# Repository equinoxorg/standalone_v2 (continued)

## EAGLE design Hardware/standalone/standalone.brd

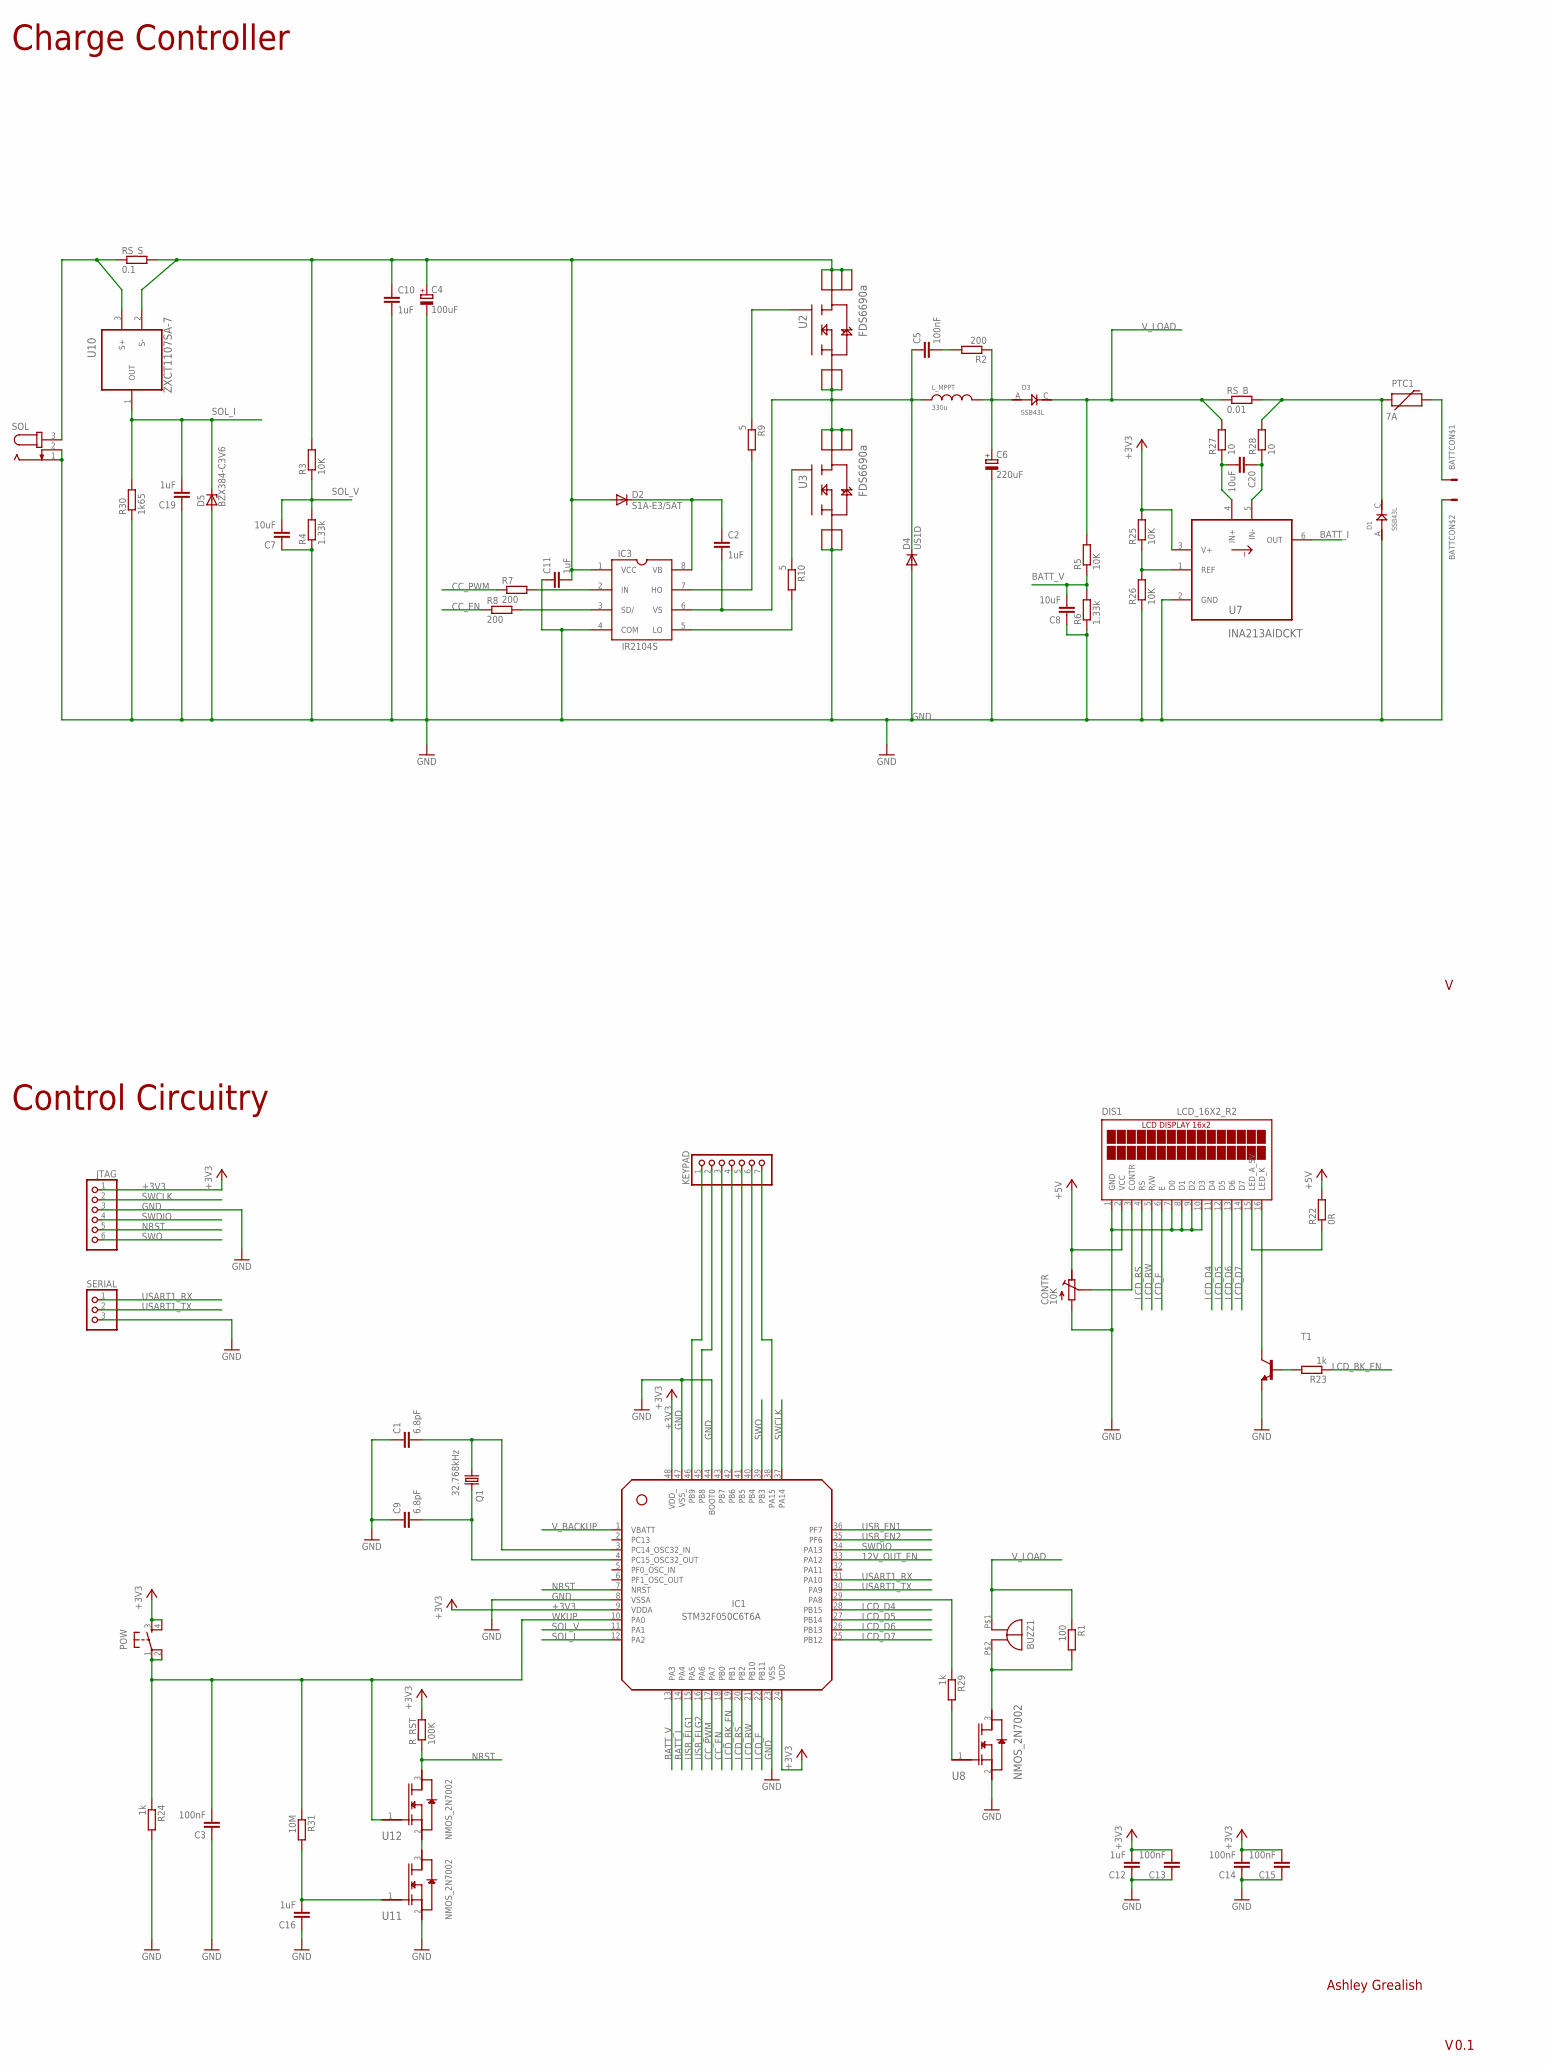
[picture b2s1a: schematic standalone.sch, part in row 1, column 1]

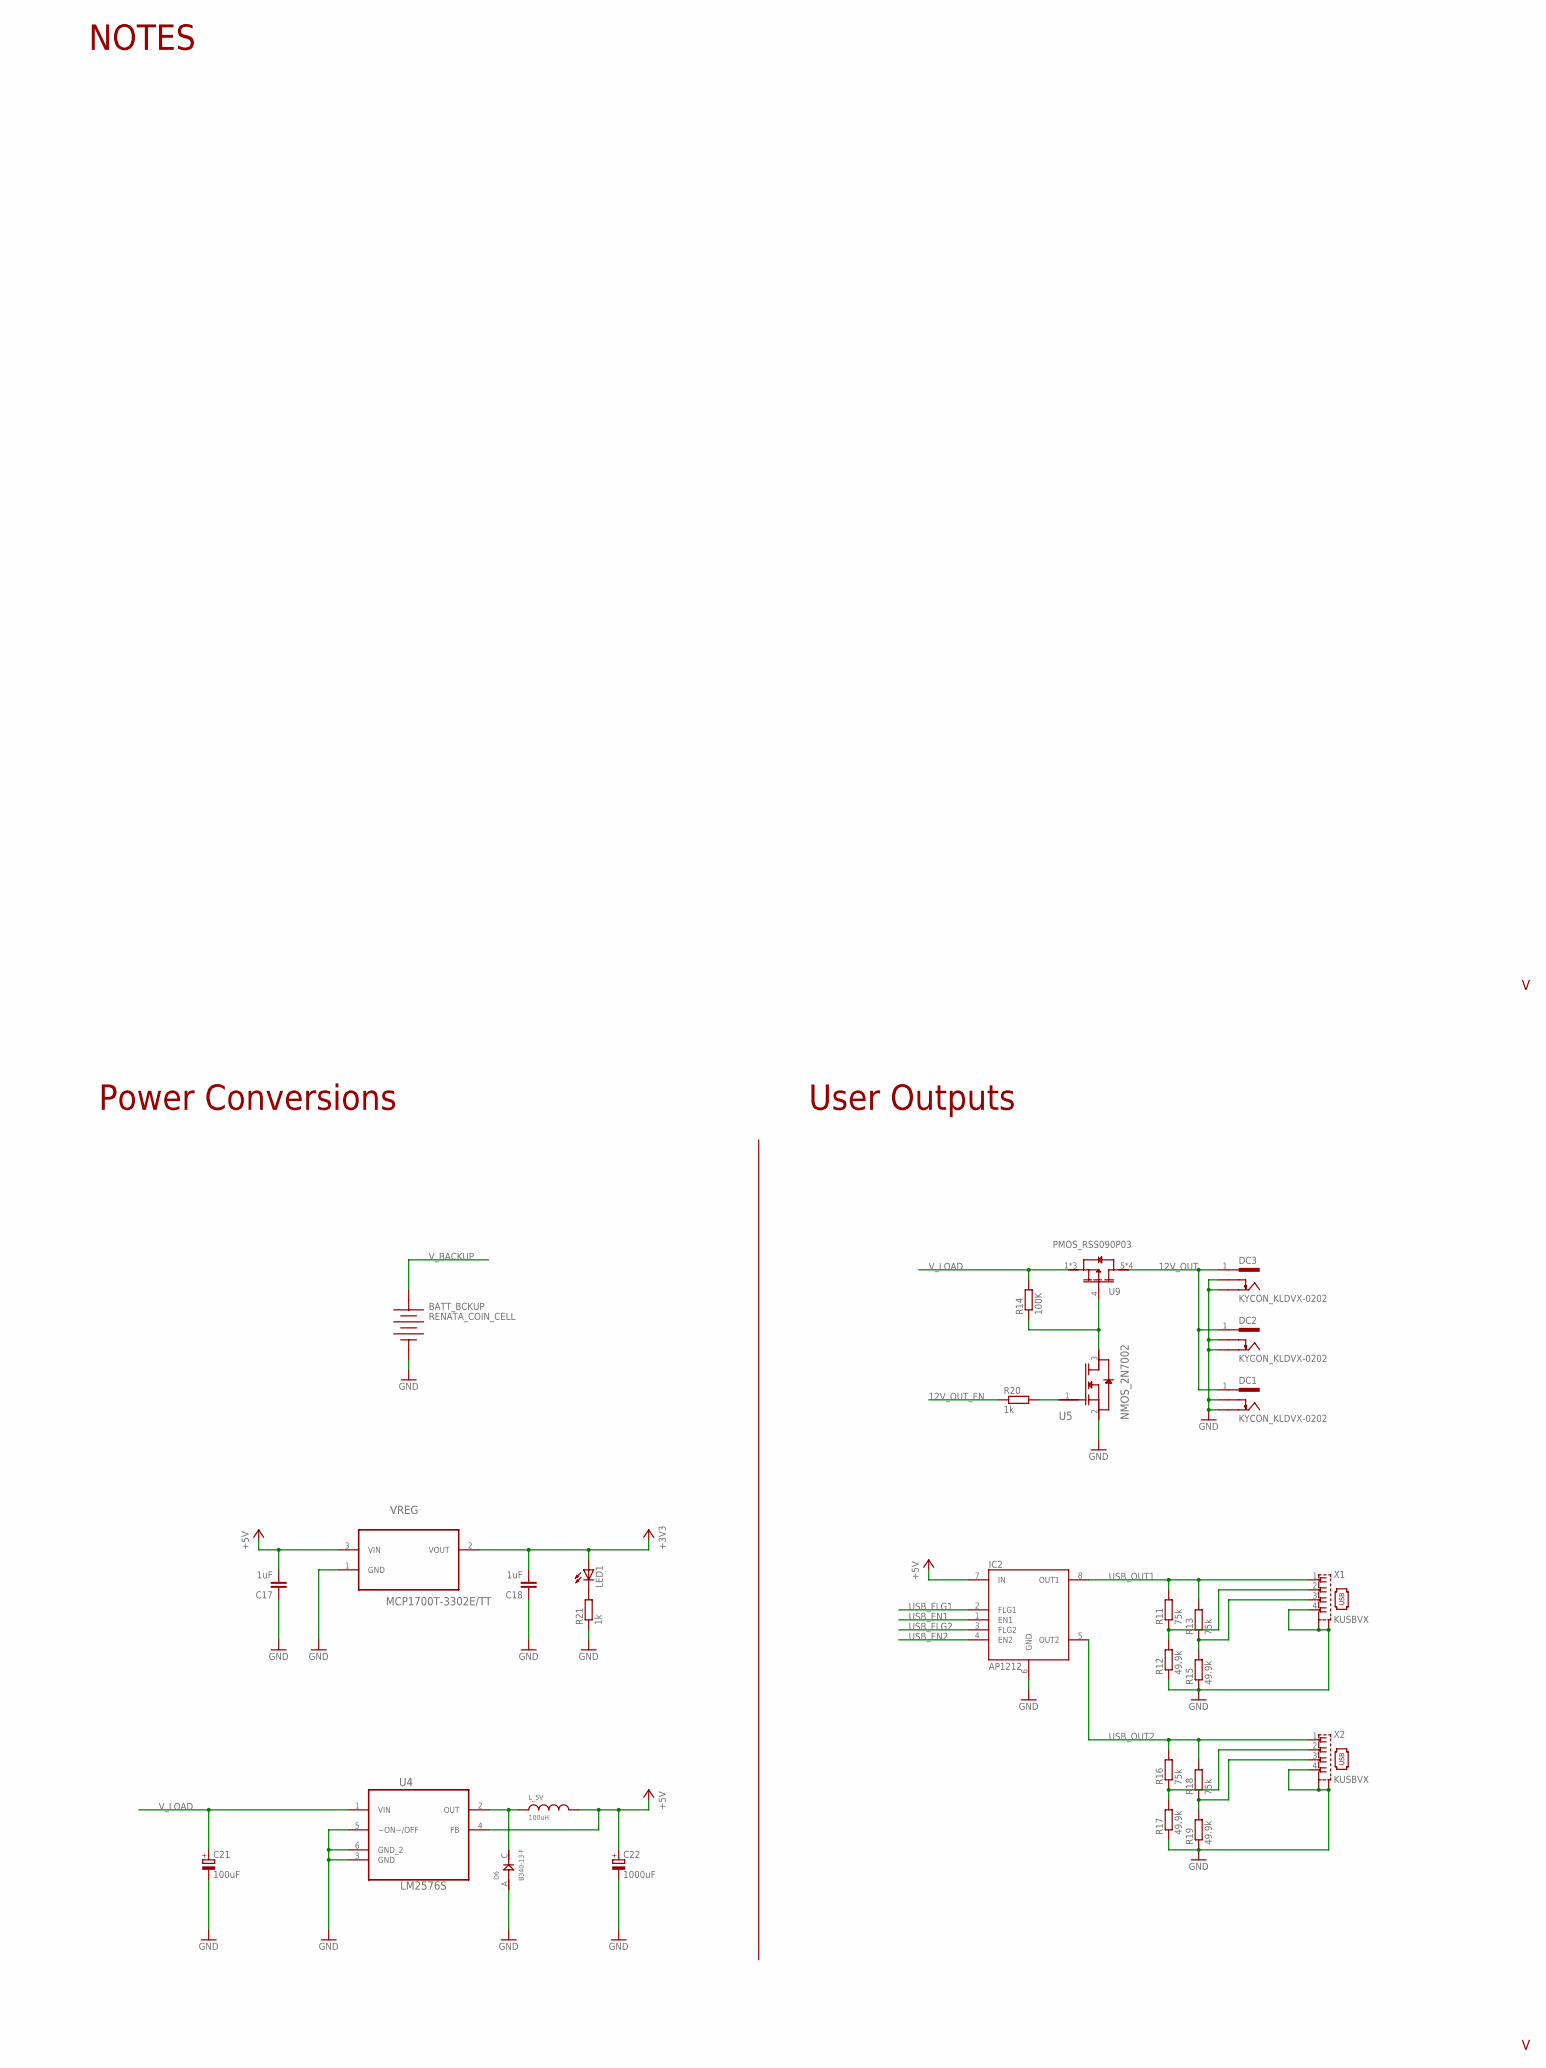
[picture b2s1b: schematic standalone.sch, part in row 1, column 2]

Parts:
BATT: CON_MOLEX_39_29_1028; MOLEX_39_29_1028
BATT_BCKUP: RENATA_COIN_CELL; PANASONIC_CR2032_1298246
BUZZ1: BUZZ_14MM; BUZZ_14MM_5M_PINS
C1, C9: 6.8pF; C0603K
C2, C10, C11, C12, C16, C17, C18, C19: 1uF; C0805K
C3, C5, C13, C14, C15: 100nF; C0805K
C4, C21: 100uF; PANASONIC_E
C6: 220uF; PANASONIC_F
C7, C8, C20: 10uF; C0805K
C22: 1000uF; PANASONIC_G
CONTR: 10K; R_TRIMM_RC33X
D1, D3: SSB43L; DO214AA
D2: S1A-E3/5AT; DO-214AC
D4: US1D; DO-214AC
D5: BZX384-C3V6; SOD323
D6: B340-13-F; SMC
DC1, DC2, DC3: KYCON_KLDVX-0202; KYCON_KLVDX_2020_B
DIS1: LCD_16X2_R2
IC1: STM32F050C6T6A; LQFP48
IC2: AP1212; SO8
IC3: IR2104S
JTAG: PINHD-1X6; 1X06
KEYPAD: PINHD-1X7/90; 1X07/90
LED1: POW_3V3; CHIPLED_0805
L_5V: 100uH; INDUC_BOURNS_SDR2207
L_MPPT: 330u; INDUC_BOURNS_SDR1806
POW: TAC_SWITCHPTH; TACTILE-PTH
PTC1: 7A; PTC_MF_R700
Q1: 32.768kHz; MC-306; MPN MC-306
R1: 100; M0805
R2, R7, R8: 200; M0805
R3, R5, R25, R26: 10K; M0805
R4, R6: 1.33k; M0805
R9, R10: 5; M0805
R11, R13, R16, R18: 75k; M0805
R12, R15, R17, R19: 49.9k; M0805
R14: 100K; M0805
R20, R21, R23, R24, R29: 1k; M0805
R22: 0R; M0805
R27, R28: 10; M0805
R30: 1k65; M0805
R31: 10M; M0805
RS_B: 0.01; R2512
RS_S: 0.1; R2512
R_RST: 100K; M0805
SERIAL: PINHD-1X3; 1X03
SOL: JACK-PLUG0; SPC4077
T1: BC847B-NPN-SOT23-BEC; SOT23-BEC
U2, U3: FDS6690a; SOIC127P600X175-8N
U4: LM2576S; TO263-5
U5: NMOS_2N7002; SOT103P240X110-3N
U7: INA213AIDCKT; SOT65P210X110-6N
U8, U11, U12: NMOS_2N7002; SOT103P240X110-3N; MPN 2N7002-7-F
U9: PMOS_RSS090P03; SO8
U10: ZXCT1107SA-7; SOT91P240X110-3N
U$1: EQUINOX_LOGO_LARGE
VREG: MCP1700T-3302E/TT; SOT95P237X112-3N
X1, X2: KUSBVX

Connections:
12V_OUT: DC1.1, DC2.1, DC3.1, U9.5 (D2), U9.6 (D2), U9.7 (D2), U9.8 (D2)
12V_OUT_EN: IC1.33 (PA12), R20.1
+3V3: C12.2, C13.2, C14.2, C15.2, C18.2, IC1.9 (VDDA), IC1.24 (VDD), IC1.48 (VDD_), JTAG.1, LED1.A, POW.3, POW.4, R25.2, R_RST.2, U7.3 (V+), VREG.2 (VOUT)
+5V: C17.2, C22.+, CONTR.CW (A), DIS1.2 (VCC), IC2.7 (IN), L_5V.P$2, R22.2, U4.4 (FB), VREG.3 (VIN)
BATT_I: IC1.14 (PA4), U7.6 (OUT)
BATT_V: C8.2, IC1.13 (PA3), R5.1, R6.2
CC_EN: IC1.18 (PB0), R8.1
CC_PWM: IC1.17 (PA7), R7.1
GND: BATT.P$2, BATT_BCKUP.P- (NEG), C1.1, C3.1, C4.-, C6.-, C7.1, C8.1, C9.1, C10.2, C11.1, C12.1, C13.1, C14.1, C15.1, C16.1, C17.1, C18.1, C19.1, C21.-, C22.-, CONTR.CCW (E), D1.A (ANODE), D4.A, D5.A, D6.A (ANODE), DC1.2, DC1.3, DC2.2, DC2.3, DC3.2, DC3.3, DIS1.1 (GND), DIS1.7 (D0), DIS1.8 (D1), DIS1.9 (D2), DIS1.10 (D3), IC1.8 (VSSA), IC1.23 (VSS), IC1.44 (BOOT0), IC1.47 (VSS_), IC2.6 (GND), IC3.4 (COM), JTAG.3, R4.1, R6.1, R12.1, R15.1, R17.1, R19.1, R21.1, R24.2, R26.1, R30.1, SERIAL.3, SOL.1, SOL.2, T1.E, U3.1 (S_2), U3.2 (S_3), U3.3 (S), U4.3 (GND), U4.5 (~ON~/OFF), U4.6 (GND_2), U5.2 (S), U7.2 (GND), U8.2 (S), U11.2 (S), VREG.1 (GND), X1.4, X1.M1 (S1), X1.M2 (S2), X2.4, X2.M1 (S1), X2.M2 (S2)
LCD_BK_EN: IC1.19 (PB1), R23.1
LCD_D4: DIS1.11 (D4), IC1.28 (PB15)
LCD_D5: DIS1.12 (D5), IC1.27 (PB14)
LCD_D6: DIS1.13 (D6), IC1.26 (PB13)
LCD_D7: DIS1.14 (D7), IC1.25 (PB12)
LCD_E: DIS1.6 (E), IC1.22 (PB11)
LCD_RS: DIS1.4 (RS), IC1.20 (PB2)
LCD_RW: DIS1.5 (R/W), IC1.21 (PB10)
unnamed: C1.2, IC1.3 (PC14_OSC32_IN), Q1.1
unnamed: CONTR.WIPE (S), DIS1.3 (CONTR)
unnamed: IC3.3 (SD/), R8.2
unnamed: D1.C (CATHODE), PTC1.P$1, R28.2, RS_B.2
unnamed: C2.2, C5.1, D4.C, IC3.6 (VS), L_MPPT.P$1, U2.1 (S_2), U2.2 (S_3), U2.3 (S), U3.5 (D_3), U3.6 (D_2), U3.7 (D_4), U3.8 (D)
unnamed: IC3.7 (HO), R9.2
unnamed: IC3.2 (IN), R7.2
unnamed: C2.1, D2.C, IC3.8 (VB)
unnamed: R10.1, U3.4 (G)
unnamed: C6.+, D3.A (ANODE), L_MPPT.P$2, R2.1
unnamed: IC3.5 (LO), R10.2
unnamed: R9.1, U2.4 (G)
unnamed: C5.2, R2.2
unnamed: C4.+, C10.1, C11.2, D2.A, IC3.1 (VCC), R3.2, RS_S.2, U2.5 (D_3), U2.6 (D_2), U2.7 (D_4), U2.8 (D), U10.2 (S-)
unnamed: C9.2, IC1.4 (PC15_OSC32_OUT), Q1.4 (2)
unnamed: DIS1.15 (LED_A_5V), R22.1
unnamed: R16.1, R17.2, X2.2
unnamed: D6.C (CATHODE), L_5V.P$1, U4.2 (OUT)
unnamed: IC1.29 (PA8), R29.1
unnamed: IC1.46 (PB9), KEYPAD.1
unnamed: IC1.45 (PB8), KEYPAD.2
unnamed: R14.1, U5.3 (D), U9.4 (G)
unnamed: IC1.43 (PB7), KEYPAD.3
unnamed: IC1.42 (PB6), KEYPAD.4
unnamed: IC1.41 (PB5), KEYPAD.5
unnamed: IC1.40 (PB4), KEYPAD.6
unnamed: IC1.38 (PA15), KEYPAD.7
unnamed: DIS1.16 (LED_K), T1.C
unnamed: R23.2, T1.B
unnamed: R11.1, R12.2, X1.2
unnamed: R13.1, R15.2, X1.3
unnamed: R20.2, U5.1 (G)
unnamed: R18.1, R19.2, X2.3
unnamed: LED1.C, R21.2
unnamed: RS_S.1, SOL.3, U10.3 (S+)
unnamed: R25.1, R26.2, U7.1 (REF)
unnamed: C20.2, R27.1, U7.4 (IN+)
unnamed: C20.1, R28.1, U7.5 (IN-)
unnamed: BUZZ1.P$2 (-), R1.2, U8.3 (D)
unnamed: R29.2, U8.1 (G)
unnamed: C16.2, R31.2, U11.1 (G)
unnamed: U11.3 (D), U12.2 (S)
unnamed: BATT.P$1, PTC1.P$2
NRST: IC1.7 (NRST), JTAG.5, R_RST.1, U12.3 (D)
SOL_I: C19.2, D5.C, IC1.12 (PA2), R30.2, U10.1 (OUT)
SOL_V: C7.2, IC1.11 (PA1), R3.1, R4.2
SWCLK: IC1.37 (PA14), JTAG.2
SWDIO: IC1.34 (PA13), JTAG.4
SWO: IC1.39 (PB3), JTAG.6
USART1_RX: IC1.31 (PA10), SERIAL.1
USART1_TX: IC1.30 (PA9), SERIAL.2
USB_EN1: IC1.36 (PF7), IC2.1 (EN1)
USB_EN2: IC1.35 (PF6), IC2.4 (EN2)
USB_FLG1: IC1.15 (PA5), IC2.2 (FLG1)
USB_FLG2: IC1.16 (PA6), IC2.3 (FLG2)
USB_OUT1: IC2.8 (OUT1), R11.2, R13.2, X1.1
USB_OUT2: IC2.5 (OUT2), R16.2, R18.2, X2.1
V_BACKUP: BATT_BCKUP.P+ (POS), IC1.1 (VBATT)
V_LOAD: BUZZ1.P$1 (+), C21.+, D3.C (CATHODE), R1.1, R5.2, R14.2, R27.2, RS_B.1, U4.1 (VIN), U9.1 (S2), U9.2 (S2), U9.3 (S2)
WKUP: C3.2, IC1.10 (PA0), POW.1, POW.2, R24.1, R31.1, U12.1 (G)

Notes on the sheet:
Charge Controller
Control Circuitry
Power Conversions
User Outputs
NOTES

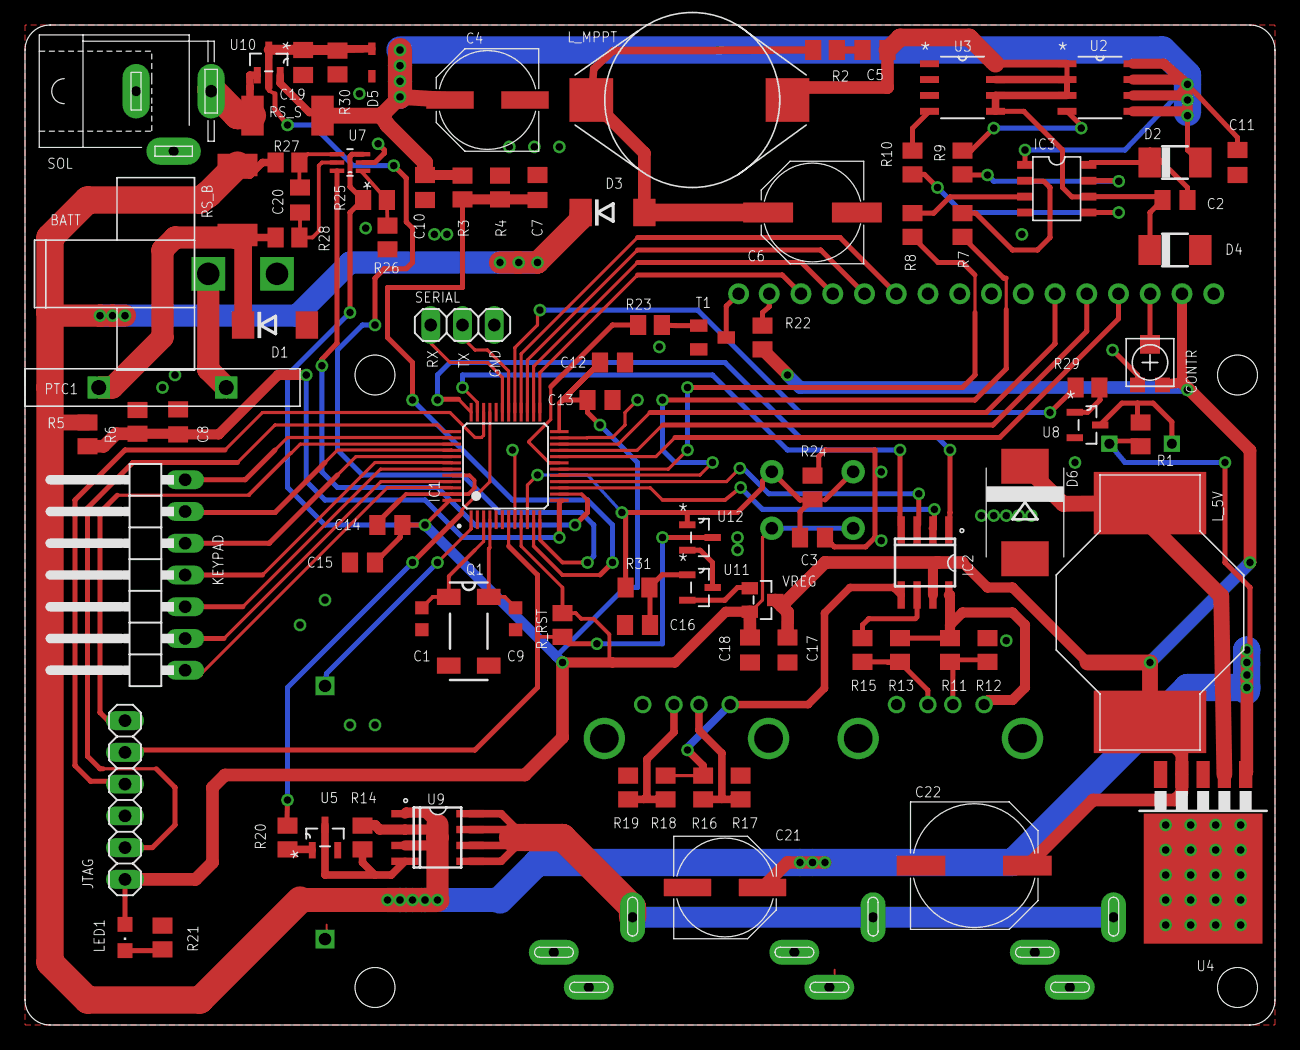
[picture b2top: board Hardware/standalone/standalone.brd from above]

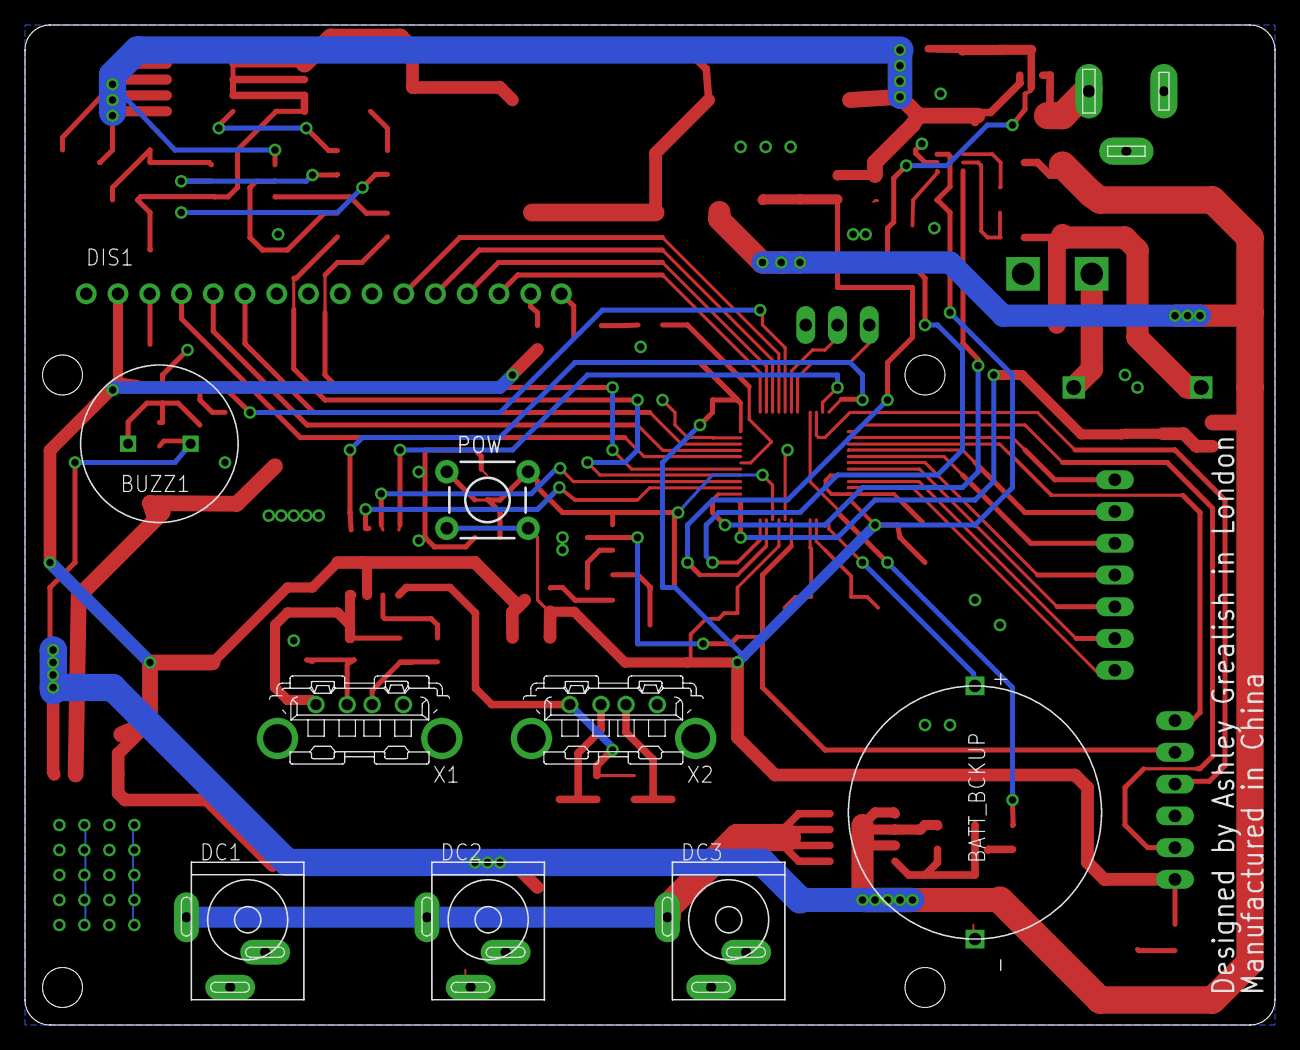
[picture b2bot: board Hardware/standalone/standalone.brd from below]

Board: 2 copper layers, 100.0 x 80.0 mm, 98 parts (10 on the bottom side), 77 nets.

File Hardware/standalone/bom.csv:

"Qty";"Value";"Device";"Package";"Parts";"Description";"FARNELL";"MF";"MPN";"OC_FARNELL";"OC_NEWARK";"PACKAGE";"SUPPLIER";
"1";"";"DIODE_VS-6CWQ03FN";"TO252";"D$1";"Datasheet: http://www.vishay.com/docs/94247/6cwq03fn.pdf";"";"";"";"";"";"";"";
"1";"";"PINHD-1X6";"1X06";"JTAG";"PIN HEADER";"";"";"";"";"";"";"";
"1";"";"PINHD-1X7/90";"1X07/90";"KEYPAD";"PIN HEADER";"";"";"";"";"";"";"";
"1";"";"TAC_SWITCHPTH";"TACTILE-PTH";"POW";"Momentary Switch";"";"";"";"";"";"";"";
"1";"";"ZENER-DIODEDO41Z10";"DO41Z10";"D5";"Z-Diode";"";"";"";"";"";"";"";
"2";"0.005";"R-EU_R2512";"R2512";"RSENSE2, RSENSE_BATT";"RESISTOR, European symbol";"";"";"";"";"";"";"";
"3";"0.1uF";"C-EUC0805K";"C0805K";"C5, C7, C8";"CAPACITOR, European symbol";"";"";"";"";"";"";"";
"1";"0R";"R-EU_M0805";"M0805";"R22";"RESISTOR, European symbol";"";"";"";"";"";"";"";
"2";"1.32k";"R-EU_M0805";"M0805";"R4, R6";"RESISTOR, European symbol";"";"";"";"";"";"";"";
"2";"100K";"R-EU_M0805";"M0805";"R14, R_RST";"RESISTOR, European symbol";"";"";"";"";"";"";"";
"4";"100nF";"C-EUC0805K";"C0805K";"C3, C13, C14, C15";"CAPACITOR, European symbol";"";"";"";"";"";"";"";
"1";"100u";"C2.5/2";"C2.5-2";"5V_CIN";"CAPACITOR";"";"";"";"";"";"";"";
"1";"100uF";"C-EU025-050X050";"C025-050X050";"C4";"CAPACITOR, European symbol";"";"";"";"";"";"";"";
"7";"10K";"R-EU_M0805";"M0805";"KEY_1, KEY_2, KEY_3, R3, R5, R_GAIN, R_GAIN1";"RESISTOR, European symbol";"";"";"";"";"";"";"";
"1";"10K";"R-TRIMM3304W";"RTRIM3304W";"CONTR";"Trimm resistor";"";"";"";"";"";"";"";
"2";"12.5pF";"C-EUC0805K";"C0805K";"C1, C9";"CAPACITOR, European symbol";"";"";"";"";"";"";"";
"3";"1k";"R-EU_M0805";"M0805";"R20, R23, R24";"RESISTOR, European symbol";"";"";"";"";"";"";"";
"7";"1uF";"C-EUC0805K";"C0805K";"C2, C10, C11, C12, C16, C17, C18";"CAPACITOR, European symbol";"";"";"";"";"";"";"";
"3";"200";"R-EU_M0805";"M0805";"R2, R7, R8";"RESISTOR, European symbol";"";"";"";"";"";"";"";
"1";"220uF";"C-EU025-050X050";"C025-050X050";"C6";"CAPACITOR, European symbol";"";"";"";"";"";"";"";
"1";"32.768khz";"CRYSTAL_CMJ206T";"CRYSTAL_CMJ206T";"Q2";"Datasheet: http://cfm.citizen.co.jp/english/product/pdf/CMJ206T.pdf";"";"";"";"";"";"";"";
"1";"330u";"C2.5/2";"C2.5-2";"5V_COUT";"CAPACITOR";"";"";"";"";"";"";"";
"2";"330uF";"INDUC_BOURNES_SDR1806";"BOURNS_SDR1806";"L_5V, U$6";"Datasheet:  http://www.bourns.com/data/global/pdfs/SDR1806.pdf";"";"";"";"";"";"";"";
"1";"470K";"R-EU_M0805";"M0805";"R1";"RESISTOR, European symbol";"";"";"";"";"";"";"";
"4";"49.9k";"R-EU_M0805";"M0805";"R12, R15, R17, R19";"RESISTOR, European symbol";"";"";"";"";"";"";"";
"2";"5";"R-EU_M0805";"M0805";"R9, R10";"RESISTOR, European symbol";"";"";"";"";"";"";"";
"4";"75k";"R-EU_M0805";"M0805";"R11, R13, R16, R18";"RESISTOR, European symbol";"";"";"";"";"";"";"";
"1";"AP1212";"AP1212";"SO8";"U$8";"Datasheet: http://www.farnell.com/datasheets/608767.pdf";"";"";"";"";"";"";"";
"1";"BUZZ_14MM";"BUZZ_14MM";"14MM_5M_PINS";"BUZZ1";"";"";"";"";"";"";"";"";
"1";"CON_MOLEX_39_29_1028";"CON_MOLEX_39_29_1028";"MOLEX_39_29_1028";"BATT";"";"";"";"";"";"";"";"";
"3";"DMS3016SSS-13";"DMS3016SSS-13";"SOIC127P600X175-8N";"U1, U2, U3";"ENHANCEMENT MODE MOSFET";"";"";"DMS3016SSS-13";"1863729";"27T2704";"SOIC-8";"DIODES INC.";
"1";"EQUINOX_LOGO_LARGE";"EQUINOX_LOGO_LARGE";"EQUINOX_LOGO_LARGE";"U$1";"";"";"";"";"";"";"";"";
"1";"IR2104S";"IR2104S";"IR2104S";"GATE_DRIVE";"Half Bridge Mosfet - IGBT driver SOIC";"";"";"";"";"";"";"";
"2";"KUSBVX";"KUSBVX";"KUSBVX";"X1, X2";"Vertical,Top Entry Universal Serial Bus Connector KUSBVX Series";"";"";"";"";"";"";"";
"3";"KYCON_KLDVX-0202";"KYCON_KLDVX-0202";"KYCON_KLVDX_2020_B";"U$2, U$3, U$4";"";"";"";"";"";"";"";"";
"1";"LCD_16X2_R2";"LCD_16X2_R2";"LCD_16X2_R2";"DIS1";"Supplier: info";"";"";"";"unknown";"unknown";"";"";
"1";"LM2575S-15";"LM2575S-15";"TO170P1435X465-6N";"U4";"Voltage Regulator";"";"";"LM2575S-15";"1798356";"75R2093";"TO-263-5";"National";
"1";"MCP1700T-3302E/TT";"MCP1700T-3302E/TT";"SOT95P237X112-3N";"U$7";"Low Quiescent Current LDO";"";"";"MCP1700T-3302E/TT";"1296592";"88H9817";"SOT23-3";"Microchip";
"2";"NMOS_2N7002";"NMOS_2N7002";"SOT103P240X110-3N";"U5, U6";"N-CHANNEL ENHANCEMENT MODE FIELD EFFECT TRANSISTOR";"";"";"2N7002-7-F";"1713823";"25R5679";"SOT-23-3";"DIODES INC.";
"1";"PMOS_RSS090P03";"PMOS_RSS090P03";"SO8";"U$9";"";"1525544";"";"";"";"";"";"";
"1";"POWER_JACK_2.1MMSLT";"POWER_JACK_2.1MMSLT";"POWER_JACK_SLOT";"SOL";"Power Jack";"";"";"";"";"";"";"";
"1";"RENATA_COIN_CELL";"PANASONIC_CR2032_1298246";"PANASONIC_CR2032_1298246";"BATT_BCKUP";"Farnell Part No: 1298246";"";"";"";"";"";"";"";
"2";"S1A-E3/5AT";"DIODE-DO-214AC";"DO-214AC";"D1, D2";"DIODE";"";"";"";"";"";"";"";
"1";"STM32F050C6T6A";"STM32F050C6T6A";"LQFP48";"U$5";"";"";"";"";"";"";"";"";
"1";"US1D - 1625280";"DIODE-DO-214AC";"DO-214AC";"D4";"DIODE";"";"";"";"";"";"";"";
"2";"ZXCT1107SA-7";"ZXCT1107SA-7";"SOT91P240X110-3N";"SENSE_AMP_BATT, SENSE_AMP_SOL";"LOW POWER HIGH-SIDE CURRENT MONITORS";"";"";"ZXCT1107SA-7";"1904027";"55T4047";"SOT-23-3";"DIODES INC.";

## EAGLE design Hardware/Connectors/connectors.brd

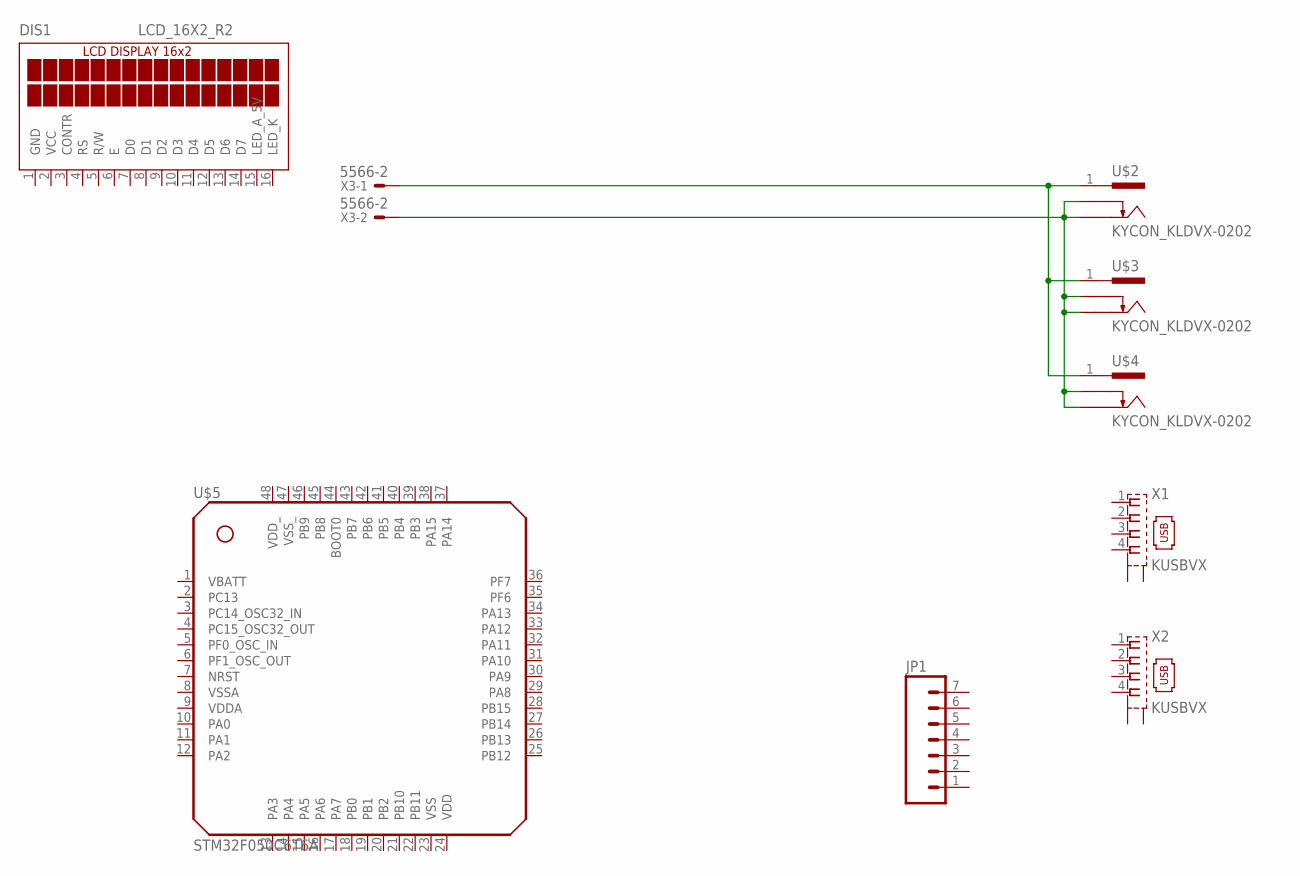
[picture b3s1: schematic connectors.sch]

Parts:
DIS1: LCD_16X2_R2
JP1: M07; 1X07
U$1: EQUINOX_LOGO_SMALL
U$2, U$3, U$4: KYCON_KLDVX-0202; KYCON_KLVDX_2020_B
U$5: STM32F050C6T6A; LQFP48
X1, X2: KUSBVX
X3: 5566-2

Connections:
GND: DIS1.1 (GND)
unnamed: U$2.1, U$3.1, U$4.1, X3.1
unnamed: U$2.2, U$2.3, U$3.2, U$3.3, U$4.2, U$4.3, X3.2
VCC: DIS1.2 (VCC)
VDD: U$5.24 (VDD)
VDD_: U$5.48 (VDD_)
VSS: U$5.23 (VSS)
VSS_: U$5.47 (VSS_)

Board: 2 copper layers, 10 parts (1 on the bottom side), 2 nets, no tracks yet.

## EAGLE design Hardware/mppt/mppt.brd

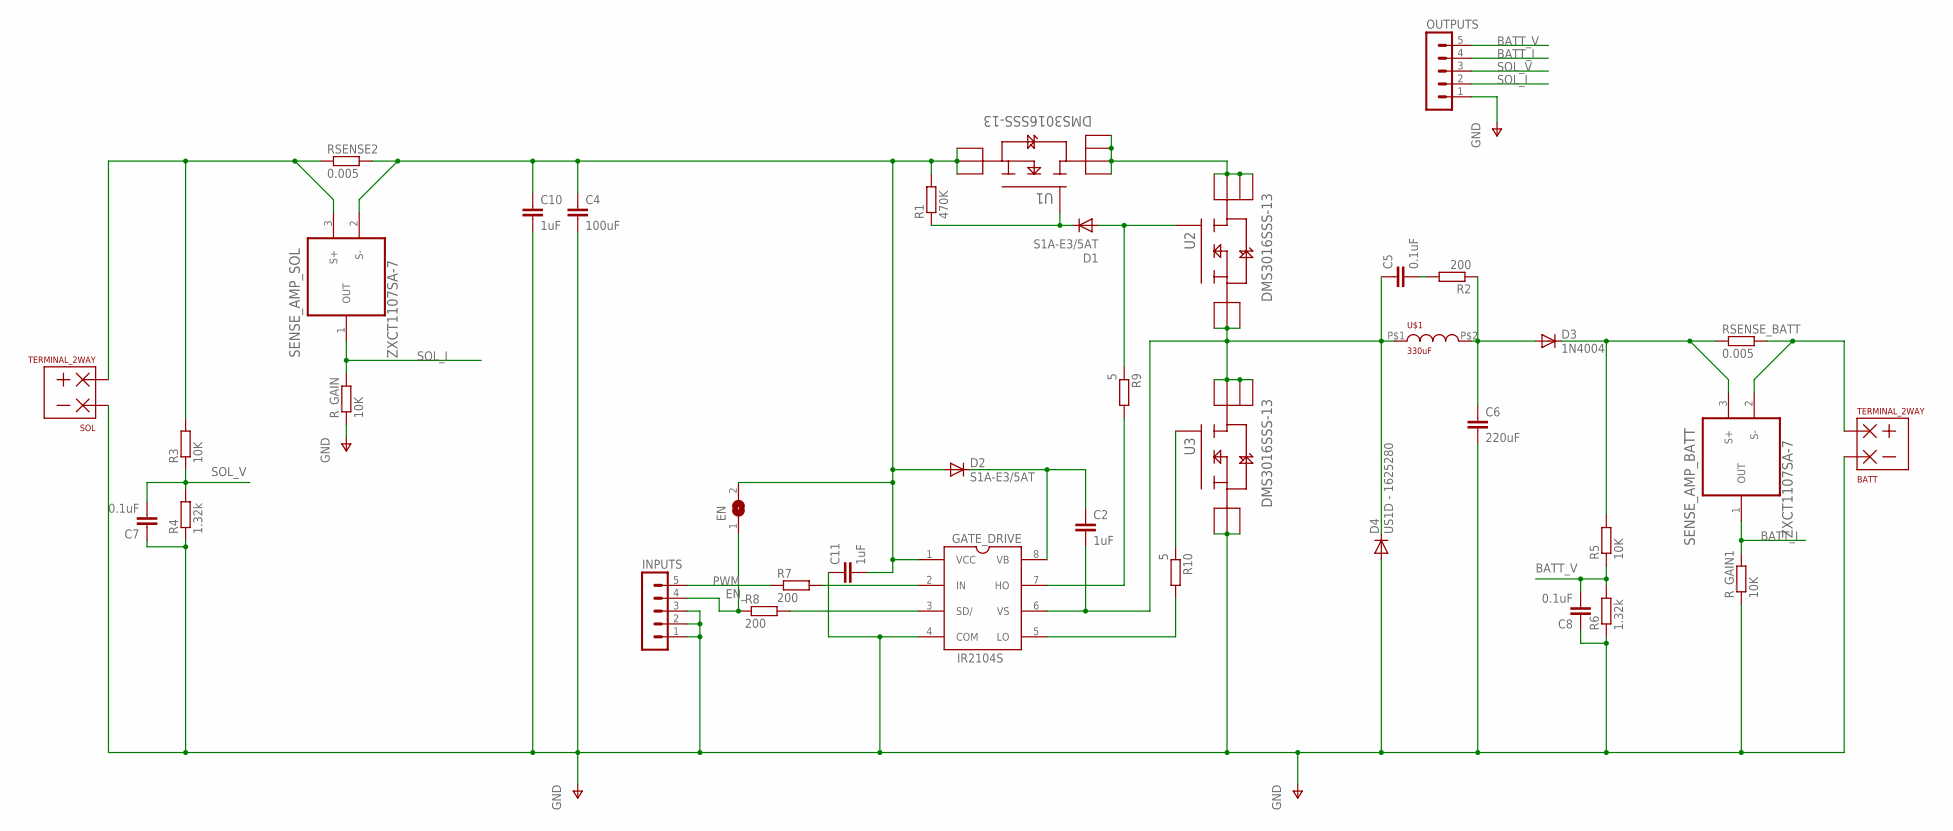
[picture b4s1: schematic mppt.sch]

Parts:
BATT: TERMINAL_2WAY
C2, C10, C11: 1uF; C0805K
C4: 100uF; C025-050X050
C5, C7, C8: 0.1uF; C0805K
C6: 220uF; C025-050X050
D1, D2: S1A-E3/5AT; DO-214AC
D3: 1N4004; DO41-10
D4: US1D - 1625280; DO-214AC
EN: SJ
GATE_DRIVE: IR2104S
INPUTS: MA05-1
OUTPUTS: MA05-1
R1: 470K; M0805
R2, R7, R8: 200; M0805
R3, R5: 10K; M0805
R4, R6: 1.32k; M0805
R9, R10: 5; M0805
RSENSE2: 0.005; R2512
RSENSE_BATT: 0.005; R2512
R_GAIN, R_GAIN1: 10K; M0805
SENSE_AMP_BATT: ZXCT1107SA-7; SOT91P240X110-3N
SENSE_AMP_SOL: ZXCT1107SA-7; SOT91P240X110-3N
SOL: TERMINAL_2WAY
U1, U2, U3: DMS3016SSS-13; SOIC127P600X175-8N
U$1: 330uF; BOURNS_SDR1806

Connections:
BATT_I: OUTPUTS.4, R_GAIN1.2, SENSE_AMP_BATT.1 (OUT)
BATT_V: C8.2, OUTPUTS.5, R5.1, R6.2
EN_: EN.1, INPUTS.4, R8.1
GND: BATT.P$2, C4.2, C6.2, C7.1, C8.1, C10.2, C11.1, D4.A, GATE_DRIVE.4 (COM), INPUTS.1, INPUTS.2, INPUTS.3, OUTPUTS.1, R4.1, R6.1, R_GAIN.1, R_GAIN1.1, SOL.P$2, U3.1 (S_2), U3.2 (S_3), U3.3 (S)
unnamed: C6.1, D3.A, R2.1, U$1.P$2
unnamed: GATE_DRIVE.3 (SD/), R8.2
unnamed: BATT.P$1, RSENSE_BATT.2, SENSE_AMP_BATT.2 (S-)
unnamed: C2.2, C5.1, D4.C, GATE_DRIVE.6 (VS), U2.1 (S_2), U2.2 (S_3), U2.3 (S), U3.5 (D_3), U3.6 (D_2), U3.7 (D_4), U3.8 (D), U$1.P$1
unnamed: D1.C, R1.1, U1.4 (G)
unnamed: U1.5 (D_3), U1.6 (D_2), U1.7 (D_4), U1.8 (D), U2.5 (D_3), U2.6 (D_2), U2.7 (D_4), U2.8 (D)
unnamed: GATE_DRIVE.7 (HO), R9.2
unnamed: GATE_DRIVE.2 (IN), R7.2
unnamed: C4.1, C10.1, C11.2, D2.A, EN.2, GATE_DRIVE.1 (VCC), R1.2, RSENSE2.2, SENSE_AMP_SOL.2 (S-), U1.1 (S_2), U1.2 (S_3), U1.3 (S)
unnamed: C2.1, D2.C, GATE_DRIVE.8 (VB)
unnamed: R10.1, U3.4 (G)
unnamed: D3.C, R5.2, RSENSE_BATT.1, SENSE_AMP_BATT.3 (S+)
unnamed: GATE_DRIVE.5 (LO), R10.2
unnamed: D1.A, R9.1, U2.4 (G)
unnamed: C5.2, R2.2
unnamed: R3.2, RSENSE2.1, SENSE_AMP_SOL.3 (S+), SOL.P$1
PWM: INPUTS.5, R7.1
SOL_I: OUTPUTS.2, R_GAIN.2, SENSE_AMP_SOL.1 (OUT)
SOL_V: C7.2, OUTPUTS.3, R3.1, R4.2

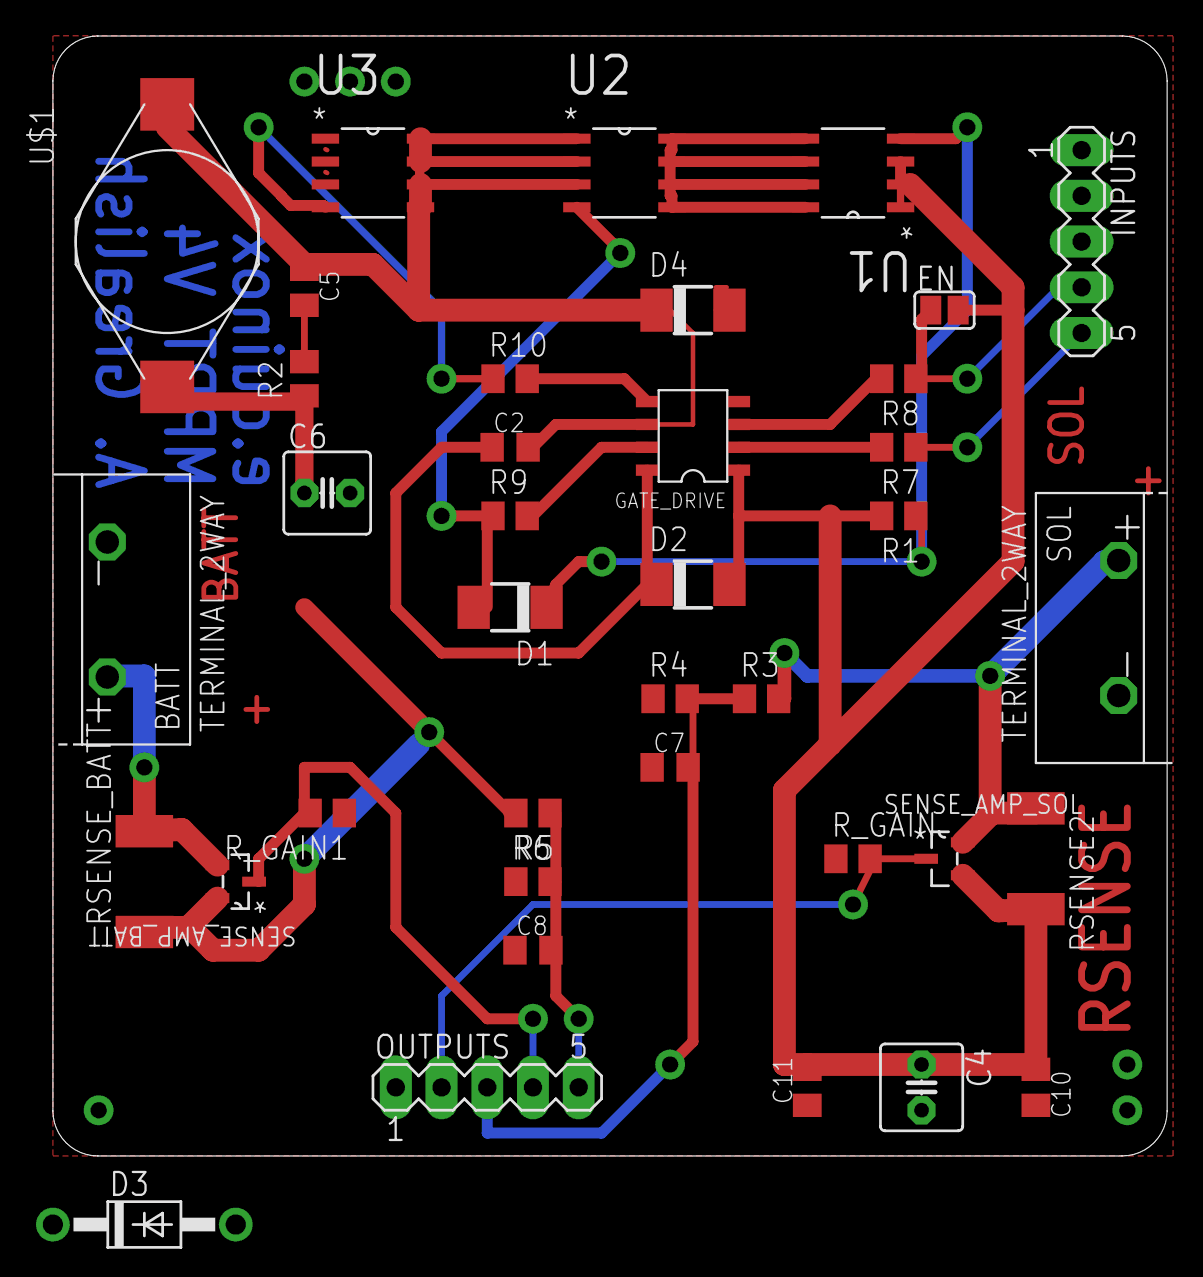
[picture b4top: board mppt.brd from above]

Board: 2 copper layers, 61.9 x 62.2 mm, 38 parts (0 on the bottom side), 23 nets.

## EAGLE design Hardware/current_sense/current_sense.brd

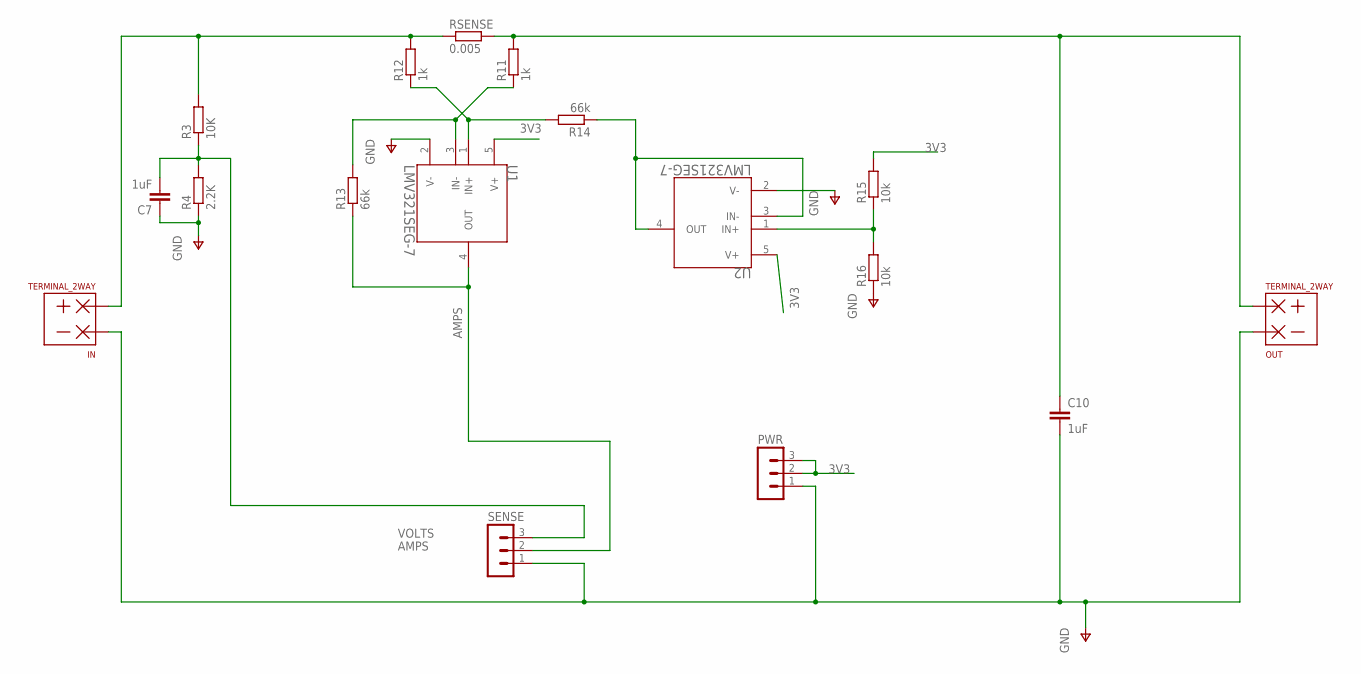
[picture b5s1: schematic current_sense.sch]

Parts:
C7, C10: 1uF; C2.5-2
IN: TERMINAL_2WAY
OUT: TERMINAL_2WAY
PWR: MA03-1
R3: 10K; M0805
R4: 2.2K; M0805
R11, R12: 1k; M0805
R13, R14: 66k; M0805
R15, R16: 10k; M0805
RSENSE: 0.005; R2512W
SENSE: MA03-1
U1: LMV321SEG-7; SOT65P210X110-5N
U2: LMV321SEG-7; SOT65P210X110-5N; MPN LMV321SEG-7

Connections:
3V3: PWR.2, PWR.3, R15.2, U1.5 (V+), U2.5 (V+)
AMPS: R13.1, SENSE.2, U1.4 (OUT)
GND: C7.1, C10.2, IN.P$2, OUT.P$2, PWR.1, R4.1, R16.1, SENSE.1
unnamed: R11.1, R13.2, U1.3 (IN-)
unnamed: R12.1, R14.2, U1.1 (IN+)
unnamed: C10.1, OUT.P$1, R11.2, RSENSE.2
unnamed: IN.P$1, R3.2, R12.2, RSENSE.1
unnamed: R15.1, R16.2, U2.1 (IN+)
unnamed: R14.1, U2.3 (IN-), U2.4 (OUT)
V-: U1.2 (V-), U2.2 (V-)
VOLTS: C7.2, R3.1, R4.2, SENSE.3
